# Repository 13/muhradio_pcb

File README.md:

# muhradio hardware carriers

KiCad 10 carrier boards for the [muhradio](https://github.com/13/muhradio)
sensor network, generated from Python scripts with KiCad's `pcbnew` API.

| Folder | Board | Role |
|--------|-------|------|
| `transmitter/cc1101/` | Arduino Pro Mini 3.3 V + CC1101 868 MHz, sensor header, battery direct on VCC | battery-powered sensor node (muhradio transmitter, CC1101) |
| `transmitter/lora/` | same carrier with a HopeRF RFM95W LoRa module (D9 RST, D2 DIO0) | battery-powered sensor node (muhradio transmitter, LoRa) |
| `receiver/cc1101/esp32s3zero/` | Waveshare ESP32-S3-Zero + CC1101 868 MHz, filtered radio supply | USB-powered gateway (muhradio receiver, env `esp32-s3-zero-cc1101`) |

Each folder has its own README, `docs/DESIGN.md`, `docs/BOM.md`, the KiCad
project and `fab/` with Gerbers and previews. Regenerate a board with
`python3 gen_board.py && python3 gen_sch.py` inside its folder, then verify
with `kicad-cli pcb drc --schematic-parity <board>.kicad_pcb`.

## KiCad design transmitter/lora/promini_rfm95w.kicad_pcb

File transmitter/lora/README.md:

# Arduino Pro Mini + RFM95W (LoRa 868 MHz) carrier PCB

A 17.78 x 60 mm two-layer carrier (v1.1, LoRa) that hard-wires an Arduino Pro Mini to the
HopeRF RFM95W LoRa module (16 x 16 mm, 16 castellations) for the muhradio
LoRa transmitter nodes. Same board size, sensor header and battery circuit as
the CC1101 carrier in `../cc1101/`; only the radio and its wiring differ.

See `docs/DESIGN.md` for the part research, the layout decision and the
assembly notes.

## Files

| File | What it is |
|------|------------|
| `promini_rfm95w.kicad_pro` | KiCad 10 project (open this) |
| `promini_rfm95w.kicad_pcb` | The board (DRC clean, ground pours filled) |
| `promini_rfm95w.kicad_sch` | Schematic (ERC clean, matches the board) |
| `promini_rfm95w.kicad_sym`, `promini_rfm95w.pretty/` | Project symbol and footprint libraries |
| `fab/gerbers/` | Gerber + Excellon drill files for ordering |
| `fab/*.png`, `fab/*.svg`, `fab/*.pdf` | Previews and the schematic PDF |
| `fab/v1.0/` | Previous revision (with the JP1 link) |
| `docs/BOM.md` | Parts list (differences from the CC1101 board) |
| `fab/drc_report.txt`, `fab/erc_report.txt` | KiCad check reports |
| `gen_board.py`, `gen_sch.py` | Scripts that regenerate the board and schematic with KiCad's Python API |

## Wiring

| Pro Mini | RFM95W | muhradio |
|----------|--------|----------|
| VCC (3.3 V) | 3.3V | |
| GND | GND | |
| D13 | SCK | |
| D12 | MISO | |
| D11 | MOSI | |
| D10 | NSS | |
| D9 | RESET | |
| D2 (INT0) | DIO0 | TX-done interrupt |
| D3 | J1 only | sensors |

DIO1..DIO5 are left unconnected (muhradio does not use them).

## Sensor header J1

`RAW  VCC  D3  SCL  SDA  GND` in one 2.54 mm row on the top side, between
the Pro Mini and the module. Matches the muhradio transmitter pinout
(I2C on A4/A5, interrupt sensors and DS18B20 on D3). Optional R1 (4.7 k,
D3 pull-up for DS18B20) and C1 (10 uF) are 0805 parts on the top side.
A4/A5 holes are at the SparkFun positions; other clones: jumper A4/A5 to
J1 SDA/SCL.

## Antenna

The RFM95W's ANT castellation (corner of the far edge) is a plated 1.0 mm
hole on the carrier: push an 86 mm solid wire through it and the castellation
and solder once.

## Battery power

2 x AA or one LiFePO4 cell straight on VCC through J2 (JST PH) and Q1 (reverse-
polarity P-FET).
Remove the Pro Mini's power LED and regulator. Unplug the battery and use a
3.3 V FTDI adapter when programming. R2 (330 R) sits in series with D3;
C2 (100 nF, DNP) is a debounce cap for reed/button nodes only.

## Measuring sleep current

There is no on-board link any more. Put the meter in series with the battery
lead at J2 (a JST PH extension cable with one wire cut is handy). Read the
sleep current there; short the meter with a jumper or clip while the node
wakes and transmits, because a meter's uA range drops volts at the 120 mA LoRa TX burst
and would brown the node out.

Use a **3.3 V / 8 MHz** Pro Mini. The CC1101 is rated 1.8-3.6 V and is not
5 V tolerant.

## Regenerating

```sh
python3 gen_board.py     # writes promini_rfm95w.kicad_pcb and the .pretty library
python3 gen_sch.py       # writes promini_rfm95w.kicad_sch and .kicad_sym
kicad-cli pcb drc --schematic-parity promini_rfm95w.kicad_pcb
```

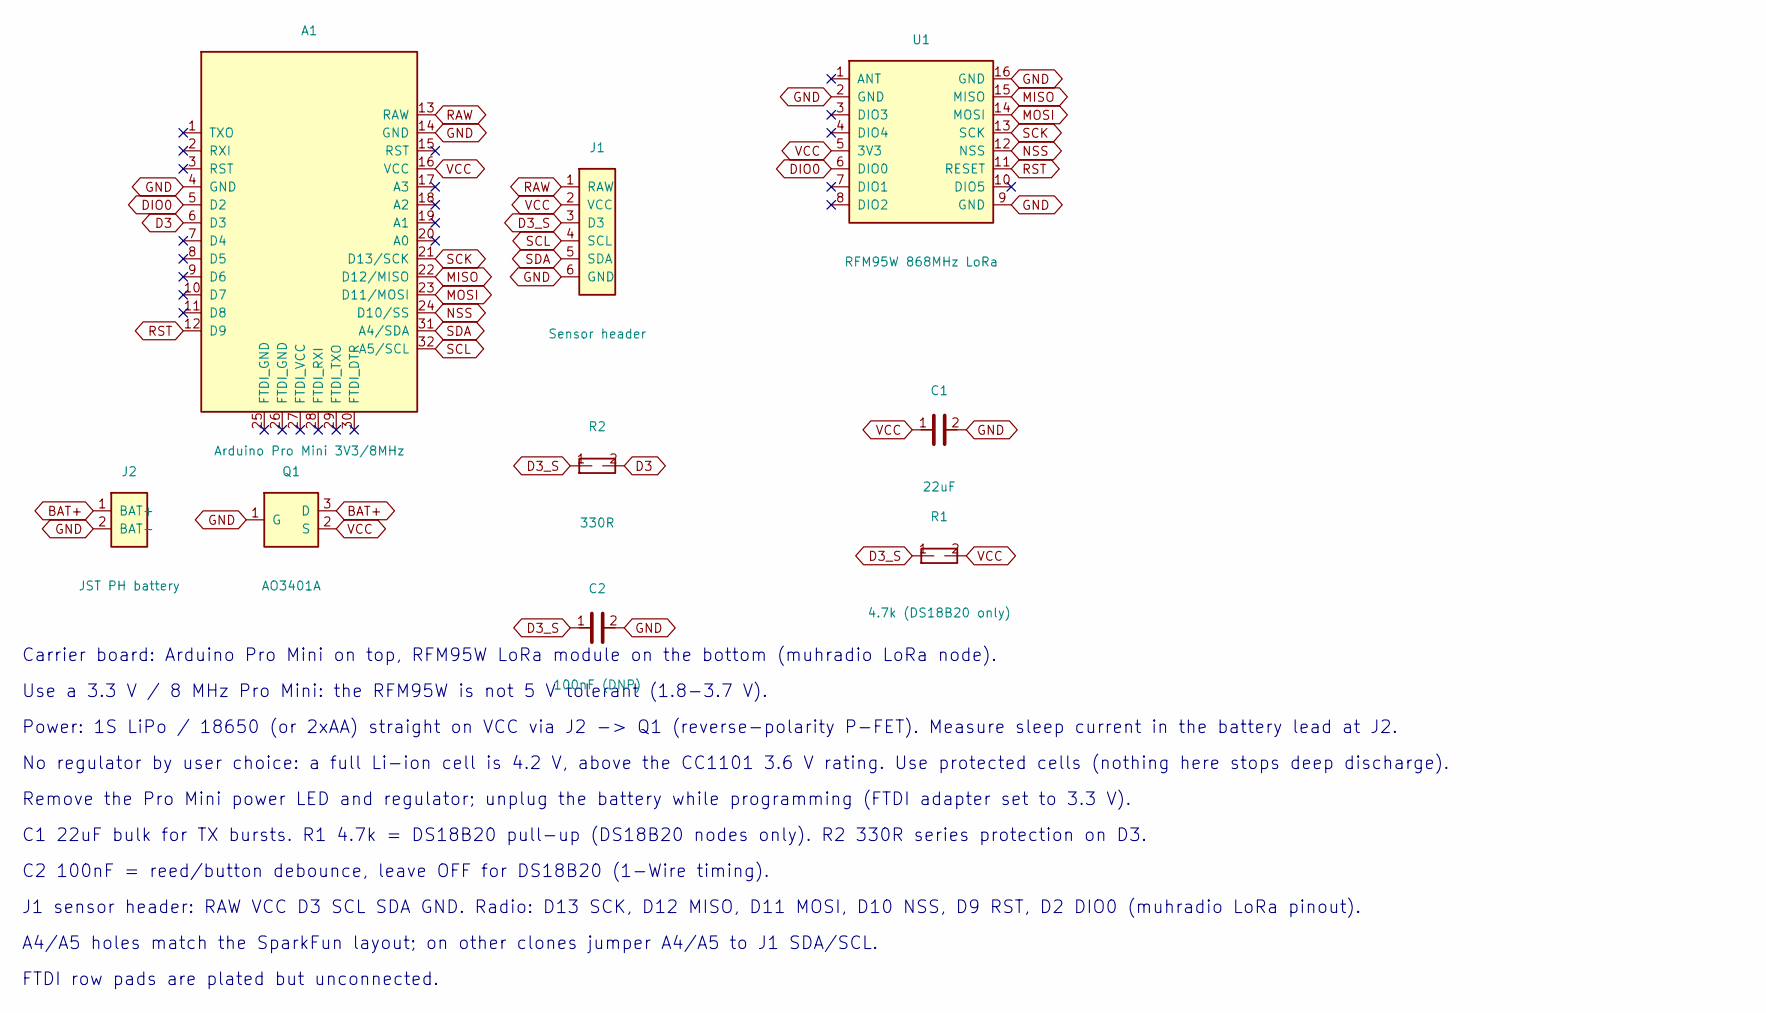
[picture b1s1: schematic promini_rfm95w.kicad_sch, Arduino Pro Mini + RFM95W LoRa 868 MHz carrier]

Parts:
A1: Arduino Pro Mini 3V3/8MHz; Arduino_Pro_Mini
C1: 22uF; C_0805
C2: 100nF (DNP); C_0805
J1: Sensor header; PinHeader_1x06_P2.54mm
J2: JST PH battery; JST_PH_S2B-PH-SM4-TB_SMD
Q1: AO3401A; SOT-23
R1: 4.7k (DS18B20 only); R_0805
R2: 330R; R_0805
U1: RFM95W 868MHz LoRa; HOPERF_RFM9XW_castellated

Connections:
BAT+: J2.1 (BAT+), Q1.3 (D)
D3: A1.6 (D3), R2.2
D3_S: C2.1, J1.3 (D3), R1.1, R2.1
DIO0: A1.5 (D2), U1.6 (DIO0)
GND: A1.4 (GND), A1.14 (GND), C1.2, C2.2, J1.6 (GND), J2.2 (BAT-), Q1.1 (G), U1.2 (GND), U1.9 (GND), U1.16 (GND)
MISO: A1.22 (D12/MISO), U1.15 (MISO)
MOSI: A1.23 (D11/MOSI), U1.14 (MOSI)
NSS: A1.24 (D10/SS), U1.12 (NSS)
RAW: A1.13 (RAW), J1.1 (RAW)
RST: A1.12 (D9), U1.11 (RESET)
SCK: A1.21 (D13/SCK), U1.13 (SCK)
SCL: A1.32 (A5/SCL), J1.4 (SCL)
SDA: A1.31 (A4/SDA), J1.5 (SDA)
VCC: A1.16 (VCC), C1.1, J1.2 (VCC), Q1.2 (S), R1.2, U1.5 (3V3)

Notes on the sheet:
Carrier board: Arduino Pro Mini on top, RFM95W LoRa module on the bottom (muhradio LoRa node).
Use a 3.3 V / 8 MHz Pro Mini: the RFM95W is not 5 V tolerant (1.8-3.7 V).
Power: 1S LiPo / 18650 (or 2xAA) straight on VCC via J2 -> Q1 (reverse-polarity P-FET). Measure sleep current in the battery lead at J2.
No regulator by user choice: a full Li-ion cell is 4.2 V, above the CC1101 3.6 V rating. Use protected cells (nothing here stops deep discharge).
Remove the Pro Mini power LED and regulator; unplug the battery while programming (FTDI adapter set to 3.3 V).
C1 22uF bulk for TX bursts. R1 4.7k = DS18B20 pull-up (DS18B20 nodes only). R2 330R series protection on D3.
C2 100nF = reed/button debounce, leave OFF for DS18B20 (1-Wire timing).
J1 sensor header: RAW VCC D3 SCL SDA GND. Radio: D13 SCK, D12 MISO, D11 MOSI, D10 NSS, D9 RST, D2 DIO0 (muhradio LoRa pinout).
A4/A5 holes match the SparkFun layout; on other clones jumper A4/A5 to J1 SDA/SCL.
FTDI row pads are plated but unconnected.

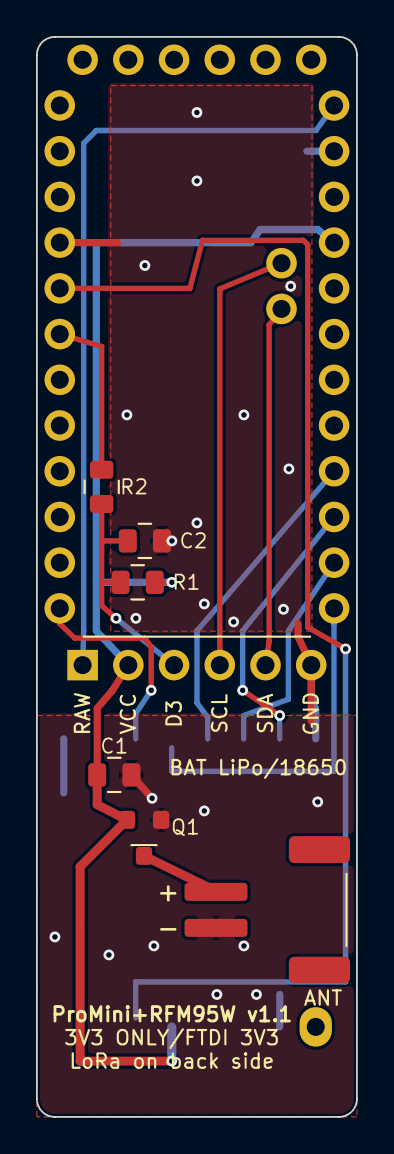
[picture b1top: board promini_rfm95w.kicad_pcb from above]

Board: 2 copper layers, 17.8 x 60.0 mm, 9 parts (1 on the bottom side), 14 nets.

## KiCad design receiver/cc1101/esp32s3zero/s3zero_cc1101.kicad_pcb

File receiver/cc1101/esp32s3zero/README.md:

# muhradio receiver carrier: ESP32-S3-Zero + CC1101 868 MHz

A 44.8 x 31 mm two-layer carrier that wires a Waveshare ESP32-S3-Zero to the
11-pin CC1101 868 MHz module exactly as the muhradio receiver firmware
expects (`receiver/platformio.ini`, env `esp32-s3-zero-cc1101` and
`esp32-s3-zero-bresser`). Both modules sit on the top side; the S3-Zero's
USB-C powers everything.

| S3-Zero | CC1101 | muhradio flag |
|---------|--------|---------------|
| GP9 | SCLK | `CC1101_SCK=9` |
| GP7 | MISO | `CC1101_MISO=7` |
| GP8 | MOSI | `CC1101_MOSI=8` |
| GP6 | CSN | `CC1101_SS=6` |
| GP2 | GDO0 | `CC1101_GDO0=2` |
| GP4 | GDO2 | spare, not used by the firmware |
| 3V3 | VCC via FB1 + C1/C2 | |
| GND | GND | |

## Files

| File | What it is |
|------|------------|
| `s3zero_cc1101.kicad_pro` / `.kicad_pcb` / `.kicad_sch` | KiCad 10 project |
| `s3zero_cc1101.kicad_sym`, `s3zero_cc1101.pretty/` | project libraries |
| `fab/gerbers/`, `fab/s3zero_cc1101_gerbers.zip` | fabrication files |
| `fab/*.png`, `fab/schematic.pdf` | previews |
| `gen_board.py`, `gen_sch.py` | regenerate everything with KiCad's Python API |
| `docs/DESIGN.md` | design decisions and part data |

## Assembly

1. Solder the CC1101 module onto its castellation pads (top side, right).
2. Solder the ESP32-S3-Zero onto its 18 pads, either flat via its castellations
   (the pads have a ledge outside the S3-Zero edge for the fillet) or on
   2.54 mm header pins.
3. FB1 (ferrite bead), C1 10 uF and C2 100 nF (all 0805) above the module.
4. Push an 86 mm solid wire through the plated ANT hole at the right edge and
   solder it; it goes through the module's ANT castellation too.
5. Two M2.5 mounting holes.

Flash with `pio run -e esp32-s3-zero-cc1101 -t upload` from the muhradio
receiver directory; no pin flags need changing.

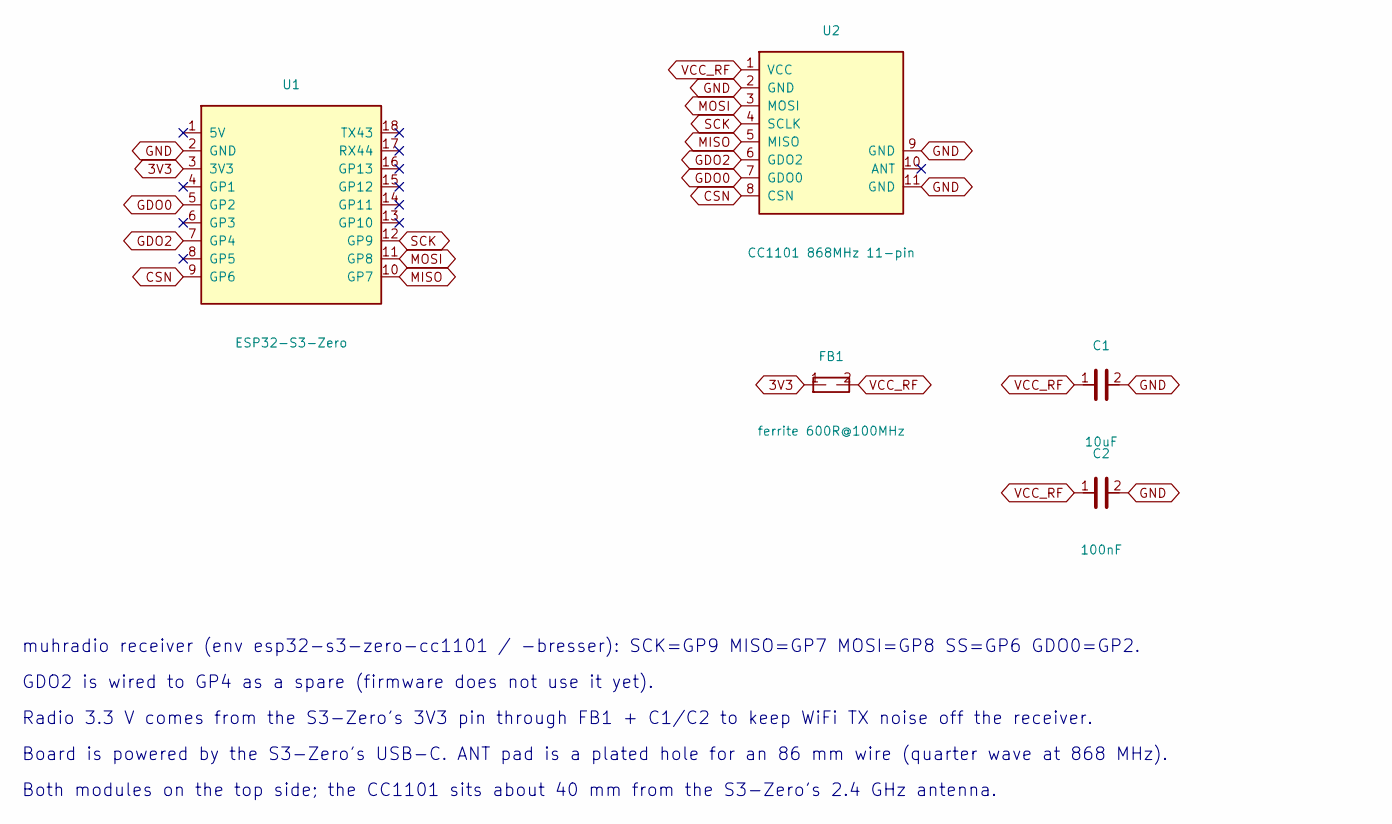
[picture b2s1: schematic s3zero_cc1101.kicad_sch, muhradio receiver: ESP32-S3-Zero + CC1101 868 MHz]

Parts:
C1: 10uF; C_0805
C2: 100nF; C_0805
FB1: ferrite 600R@100MHz; R_0805
U1: ESP32-S3-Zero; Waveshare_ESP32-S3-Zero
U2: CC1101 868MHz 11-pin; CC1101_11pin_castellated

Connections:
3V3: FB1.1, U1.3 (3V3)
CSN: U1.9 (GP6), U2.8 (CSN)
GDO0: U1.5 (GP2), U2.7 (GDO0)
GDO2: U1.7 (GP4), U2.6 (GDO2)
GND: C1.2, C2.2, U1.2 (GND), U2.2 (GND), U2.9 (GND), U2.11 (GND)
MISO: U1.10 (GP7), U2.5 (MISO)
MOSI: U1.11 (GP8), U2.3 (MOSI)
SCK: U1.12 (GP9), U2.4 (SCLK)
VCC_RF: C1.1, C2.1, FB1.2, U2.1 (VCC)

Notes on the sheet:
muhradio receiver (env esp32-s3-zero-cc1101 / -bresser): SCK=GP9 MISO=GP7 MOSI=GP8 SS=GP6 GDO0=GP2.
GDO2 is wired to GP4 as a spare (firmware does not use it yet).
Radio 3.3 V comes from the S3-Zero's 3V3 pin through FB1 + C1/C2 to keep WiFi TX noise off the receiver.
Board is powered by the S3-Zero's USB-C. ANT pad is a plated hole for an 86 mm wire (quarter wave at 868 MHz).
Both modules on the top side; the CC1101 sits about 40 mm from the S3-Zero's 2.4 GHz antenna.

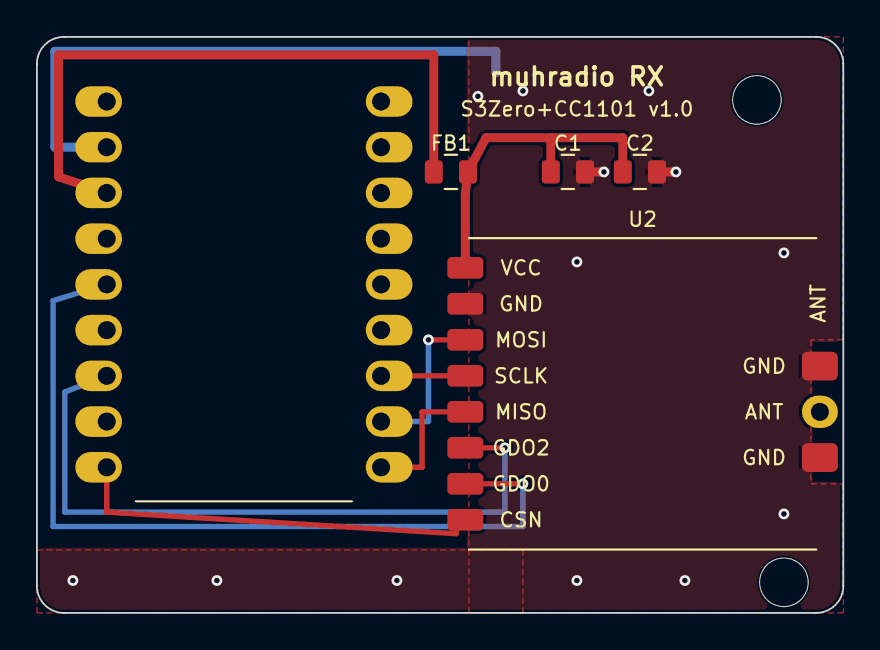
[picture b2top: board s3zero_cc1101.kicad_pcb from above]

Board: 2 copper layers, 44.8 x 32.0 mm, 7 parts (0 on the bottom side), 9 nets.

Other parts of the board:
H1, H2: M2.5; MountingHole_2.7mm

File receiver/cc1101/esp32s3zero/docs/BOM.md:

# Parts list: receiver carrier (ESP32-S3-Zero + CC1101)

Links are search pages, not vetted listings.

| Ref | Qty | Part | Package | What to check | Amazon.it | AliExpress |
|-----|-----|------|---------|---------------|-----------|------------|
| PCB | 1 | This carrier, 2 layers, 1.6 mm, 44.8 x 32 mm | – | Upload `fab/s3zero_cc1101_gerbers.zip` to JLCPCB / PCBWay | – | – |
| U1 | 1 | Waveshare ESP32-S3-Zero | module | Must be the Waveshare "Zero" (18 x 23.5 mm, 2x9 castellated). Not the Super Mini | [search](https://www.amazon.it/s?k=waveshare+esp32-s3-zero) | [search](https://www.aliexpress.com/w/wholesale-waveshare-esp32-s3-ze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 |
| U2 | 1 | CC1101 868 MHz module, 11 pin | castellated | Same module as the transmitter | [search](https://www.amazon.it/s?k=cc1101+868mhz+modulo) | [search](https://www.aliexpress.com/w/wholesale-cc1101-868mhz-11pin.html) |
| FB1 | 1 | Ferrite bead 600 R @ 100 MHz, >= 0.5 A | 0805 | e.g. BLM21PG601SN1 | [search](https://www.amazon.it/s?k=0805+ferrite+bead+600r) | [search](https://www.aliexpress.com/w/wholesale-0805-ferrite-bead-600r.html) |
| C1 | 1 | 10 uF X5R 10 V | 0805 | | [search](https://www.amazon.it/s?k=0805+10uf+x5r) | [search](https://www.aliexpress.com/w/wholesale-0805-10uf-x5r.html) |
| C2 | 1 | 100 nF X7R | 0805 | | [search](https://www.amazon.it/s?k=0805+capacitor+kit) | [search](https://www.aliexpress.com/w/wholesale-0805-capacitor-kit.html) |
| ANT | 1 | 86 mm solid wire | – | Through the plated ANT hole | – | – |
| – | opt | 2 x 9-pin 2.54 mm header (if not soldering the S3-Zero flat) | THT | | [search](https://www.amazon.it/s?k=pin+header+2.54mm+male) | [search](https://www.aliexpress.com/w/wholesale-2.54mm-pin-header-mal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 |
| – | 2 | M2.5 screws / standoffs | – | Mounting holes are 2.7 mm | – | – |

Power: the S3-Zero's USB-C (5 V). No other supply parts are needed.
